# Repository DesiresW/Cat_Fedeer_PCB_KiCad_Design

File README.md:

# Comedero inteligente para gatos — PCB custom ESP32

## Descripción general

Este repositorio contiene el diseño de una **PCB custom basada en ESP32-S3** para un prototipo de comedero inteligente para gatos. El objetivo del proyecto no es construir una tarjeta de desarrollo genérica, sino una placa funcional orientada a controlar actuadores, leer sensores y permitir el monitoreo del comportamiento de alimentación de una mascota.

La PCB integra alimentación, programación, conexiones para sensores y actuadores, y módulos externos necesarios para el sistema. El diseño está pensado como una base de prototipado: permite validar el hardware, probar la lógica de control, registrar eventos y preparar una arquitectura donde el firmware pueda incorporar alertas o modelos simples de interpretación de comportamiento.

## Objetivo del proyecto

Diseñar y fabricar una PCB compacta, funcional y soldable que sirva como núcleo electrónico de un comedero para gatos con:

- Control de suministro sólido mediante servomotores.
- Control de motobomba para suministro líquido o sistema auxiliar.
- Medición de distancia mediante sensores ultrasónicos.
- Medición de peso mediante celda de carga y módulo HX711.
- Identificación mediante NFC.
- Alimentación regulada para el ESP32 y periféricos.
- Conexión de desarrollo separada de la conexión pensada para uso final.
- Posibilidad de integrar lógica de alertas e IA embebida en el firmware.

## Esquematico

## Estado actual

El proyecto se encuentra en fase de **prototipado físico**. La PCB ya fue diseñada, fabricada, soldada y puesta en pruebas iniciales. Aún se deben validar ajustes eléctricos, mecánicos y de distribución de pines, especialmente en los elementos que dependen de integración con sensores, actuadores y carcasa.

Este repositorio documenta el diseño actual, pero no debe asumirse como una versión final de producto.

## Arquitectura general del sistema

El sistema se organiza alrededor de un microcontrolador ESP32-S3, que actúa como núcleo de control y procesamiento. La placa conecta módulos externos y componentes SMD para manejar lectura sensórica, accionamiento y alimentación.

```text
                 ┌────────────────────────┐
                 │        ESP32-S3         │
                 │  Control + firmware     │
                 └───────────┬────────────┘
                             │
        ┌────────────────────┼────────────────────┐
        │                    │                    │
 ┌──────▼──────┐      ┌──────▼──────┐      ┌──────▼──────┐
 │ Ultrasonido │      │ HX711 +     │      │ PN532 NFC   │
 │ HC-SR04 x2  │      │ celda 1 kg  │      │ + tags NFC  │
 └─────────────┘      └─────────────┘      └─────────────┘
        │                    │                    │
        └────────────────────┼────────────────────┘
                             │
                 ┌───────────▼───────────┐
                 │ Actuadores             │
                 │ Servos + motobomba     │
                 └───────────────────────┘
```

## Funcionalidades previstas

### 1. Control de actuadores

La PCB contempla conexiones para servomotores y para una motobomba controlada mediante MOSFET NMOS. La intención es separar claramente las cargas de potencia del núcleo lógico del ESP32, evitando exigir corriente desde pines o líneas que no están diseñadas para eso.

Los servomotores se plantean para mecanismos de apertura, cierre o dosificación. La motobomba se contempla como actuador auxiliar para suministro líquido o pruebas de dispensación controlada.

### 2. Medición de distancia

Se decidió usar **dos sensores ultrasónicos HC-SR04** en lugar de sensores infrarrojos de bajo costo. La decisión se tomó porque los ultrasónicos entregan una lectura continua de distancia, mientras que varios sensores infrarrojos comerciales económicos solo entregan una señal binaria ajustada por umbral.

En este prototipo, una lectura continua resulta más útil para interpretar niveles, presencia o variaciones en superficies irregulares. Además, el costo de los ultrasónicos era considerablemente menor frente a algunos sensores infrarrojos disponibles comercialmente.

### 3. Medición de peso

El sistema contempla una celda de carga de 1 kg conectada a un módulo HX711. Esta etapa permite medir cambios de peso asociados al alimento o al recipiente.

En este diseño, las conexiones entre la celda de carga y la tarjeta HX711 se consideran externas al esquemático principal de la PCB, por lo que deben revisarse directamente según el módulo y la celda utilizados.

### 4. Identificación NFC

El módulo PN532 y los tags NFC se contemplan para identificación. En el contexto del comedero, esto puede utilizarse para asociar una mascota, un recipiente, una tarjeta de configuración o un evento específico del sistema.

La implementación final depende del firmware y del flujo de uso definido para el prototipo.

### 5. Firmware e IA embebida

El hardware está pensado para recopilar datos de sensores y habilitar una capa de interpretación en firmware. La IA no toma decisiones críticas de control por sí sola; su función prevista es apoyar la clasificación de eventos y generar alertas.

Una posible clasificación de comportamiento puede incluir:

- Estado normal o sin alerta.
- Posible hambre posterior al suministro.
- Rechazo de comida.
- Consumo menor al esperado.
- Consumo mayor al esperado.
- Comportamiento atípico.

Las decisiones de seguridad, apertura, suministro adicional o activación de actuadores deben permanecer en lógica convencional validada.

## Diseño de PCB

### Enfoque

El diseño no busca replicar una DevKit comercial. La PCB fue concebida como una tarjeta específica para el comedero, con las conexiones necesarias para el proyecto y con separación entre uso final y desarrollo.

El diseño prioriza:

- Integración del ESP32-S3 como microcontrolador principal.
- Conexiones para módulos externos.
- Alimentación regulada a 3.3 V.
- Línea de 5 V para periféricos que lo requieran.
- Protección básica en líneas de alimentación y actuadores.
- Componentes SMD para reducir volumen y mejorar integración.
- Conexión de programación separada para facilitar pruebas.

### Conexión de programación

La placa incluye una conexión pensada para desarrollo/programación mediante módulo externo tipo Pololu USB-C. A diferencia de los headers de sensores y actuadores, este conector se mantiene como **macho**, porque es una conexión móvil de desarrollo.

Esta decisión permite conservar una separación entre la interfaz técnica de programación y las conexiones que usaría un usuario final.

### Headers y conectores

Para las footprints de headers se recomienda mantener la lógica definida en el prototipo:

- Headers de sensores y actuadores: **SMD y hembra**.
- Header de programación Pololu: **macho**, con footprint modificada y funcional.
- Verificar siempre el orden de pines de la huella contra el pinout real del módulo, sensor o actuador.

Este punto es crítico porque algunos módulos comerciales no respetan el mismo orden de pines entre fabricantes o versiones.

### Etiquetado de señales

Los labels del diseño se dejaron referenciando al **componente** y no necesariamente al GPIO final. Esta decisión facilita el ruteo y permite cambiar GPIOs durante la organización de pistas sin perder claridad funcional.

Por eso, antes de cerrar una nueva versión, debe revisarse la correspondencia final entre:

- Label del esquemático.
- GPIO asignado.
- Pin físico del ESP32.
- Conector o módulo externo.
- Definición usada en firmware.

## Fabricación de la PCB

La PCB fue fabricada mediante un proceso de prototipado con máquina de fibra. El flujo usado fue:

1. Definición de pistas sobre cobre mediante máquina de fibra.
2. Aplicación de máscara de soldadura sobre la placa.
3. Segunda pasada con la máquina de fibra para retirar la máscara únicamente sobre los pads.
4. Soldadura de componentes SMD y módulos de conexión.
5. Pruebas iniciales de alimentación y funcionamiento.

Este proceso permitió obtener una placa física soldable sin depender de un servicio industrial tradicional de fabricación de PCBs, aunque requiere especial cuidado en pads, continuidad, máscara y tolerancias de soldadura.

## Componentes principales

| Bloque | Componente | Función |
|---|---|---|
| Control | ESP32-S3-WROOM-1-N8R8 | Microcontrolador principal del sistema |
| Alimentación | AMS1117-3.3 | Regulación de 5 V a 3.3 V |
| Programación | Pololu USB-C | Conexión de alimentación/programación para desarrollo |
| Identificación | PN532 NFC | Lectura NFC/RFID |
| Identificación | Tags NTAG213 | Etiquetas NFC para identificación |
| Distancia | HC-SR04 x2 | Medición continua de distancia |
| Peso | HX711 | Conversión y amplificación para celda de carga |
| Peso | Celda de carga 1 kg | Medición de peso |
| Actuación | Servomotores | Apertura/cierre/dosificación |
| Actuación | Motobomba | Suministro líquido o función auxiliar |
| Potencia | AO3400 | Conmutación de motobomba |
| Protección | SS34 | Diodo Schottky para protección |
| Filtrado | Capacitores 100 nF, 10 uF, 470 uF | Estabilidad y desacople |
| Señalización | LEDs SMD | Indicadores de 5 V y 3.3 V |
| Control manual | Pulsadores SMD | Reset y modo programación |

## Lista de referencias de compra

Estos enlaces son referencias de los componentes utilizados o considerados durante el prototipo. Antes de comprar o fabricar una nueva versión, se debe verificar disponibilidad, encapsulado, dimensiones y compatibilidad con la footprint usada en KiCad.

| Componente | Referencia / enlace |
|---|---|
| PN532 NFC | https://www.mercadolibre.com.co/kit-modulo-leitor-rfid-nfc-pn532-com-tag-e-carto/p/MCO2039743778 |
| Tags NFC NTAG213 | https://www.sigmaelectronica.net/producto/ntag213-nfc/ |
| Condensador 470 uF 6.3 V SMD | https://www.sigmaelectronica.net/producto/ct2917-470uf6-3v/ |
| Sensor ultrasónico HC-SR04 | https://www.sigmaelectronica.net/producto/hc-sr04/ |
| Tarjeta HX711 | https://www.sigmaelectronica.net/producto/tarjeta-hx711/ |
| Celda de carga 1 kg | https://www.sigmaelectronica.net/producto/celda-1k/ |
| Diodo SS34 | https://www.sigmaelectronica.net/producto/ss34/ |
| MOSFET AO3400 | https://www.mercadolibre.com.co/mosfet-ao3400-a09t-sot23-smd-x-5-unidades/up/MCOU3179338761 |
| Resistencia SMD 220 Ω | https://www.sigmaelectronica.net/producto/r1206-220-ohm/ |
| Resistencia SMD 1 kΩ | https://www.sigmaelectronica.net/producto/r0805-1k/ |
| Resistencia SMD 1.96 kΩ | https://www.sigmaelectronica.net/producto/p1-96kect/ |

## Inventario resumido de soldables

La siguiente lista resume los elementos principales identificados para fabricación de varias unidades del prototipo. Las cantidades exactas deben revisarse contra el Excel de inventario y la versión actual del esquemático.

| Elemento | Valor / referencia | Encapsulado o formato | Cantidad por PCB |
|---|---:|---|---:|
| Capacitor | 0.1 uF | 0603 | 6 |
| Capacitor | 10 uF | 1206 | 3 |
| Capacitor | 470 uF | SMD | 3 |
| LED | Rojo | 0805 | 1 |
| LED | Verde | 0805 | 1 |
| Diodo | SS34 | SMC / DO-214AB | 1 |
| Header macho | Programación | SMD, mínimo 8 pines | 1 |
| Header hembra | 3 pines | SMD | 2 |
| Header hembra | 4 pines | SMD | 4 |
| Header hembra | 2 pines | SMD | 1 |
| Conector/fuente | JRC-B008 | SMD | 1 |
| MOSFET | AO3400A | SOT-23 | 1 |
| Resistencia | 10 kΩ | 0603 | 5 |
| Resistencia | 120 Ω | 1206 | 1 |
| Resistencia | 68 Ω | 1206 | 1 |
| Resistencia | 330 Ω | 0805 | 2 |
| Resistencia | 220 Ω | 1206 | 1 |
| Resistencia | 1.96 kΩ | 1206 | 2 |
| Resistencia | 1 kΩ | 0805 | 2 |
| Pulsador | Switch SMD | SMD | 2 |
| Regulador | AMS1117-3.3 | SOT-223-3 | 1 |
| MCU | ESP32-S3-WROOM-1-N8R8 | Módulo SMD | 1 |

## Módulos externos considerados

| Módulo | Cantidad por PCB | Observación |
|---|---:|---|
| PN532 NFC | 1 | Módulo externo para lectura NFC |
| Motobomba | 1 | Controlada mediante MOSFET |
| HC-SR04 | 2 | Lecturas continuas de distancia |
| Celda de carga | 1 | Conectada al HX711 |
| HX711 | 1 | Módulo de lectura para celda de carga |
| Pololu programador | 1 | Uso de desarrollo/programación |
| Header hembra Pololu | 1 | Revisar orientación y pinout |
| Servomotores | 2 | Conectores dedicados |

## Recomendaciones de diseño y revisión

### Footprints

Antes de fabricar una nueva revisión de la PCB, revisar cuidadosamente:

- Que el encapsulado del componente comprado coincida con la footprint usada.
- Que las resistencias y capacitores SMD coincidan en tamaño real con el diseño.
- Que los headers SMD tengan la orientación correcta.
- Que el orden de pines de cada módulo coincida con la huella.
- Que los pads expuestos después de la máscara de soldadura sean suficientes para soldar cómodamente.
- Que el módulo ESP32 tenga área libre adecuada para antena.

### Inventario y Excel

Para actualizar el Excel del proyecto, conviene agrupar los componentes por valor y encapsulado. No es necesario repetir cada resistencia o capacitor en filas separadas si tienen el mismo valor y la misma footprint.

Una estructura útil sería:

| Componente | Valor | Encapsulado | Cantidad por PCB | Cantidad a fabricar | Total requerido | Disponible | Faltante | Tienda | Link |
|---|---|---|---:|---:|---:|---:|---:|---|---|

También es recomendable separar la lista por tienda:

- Sigma Electrónica: mayoría de resistencias, capacitores, sensores y módulos.
- Mercado Libre: PN532 y MOSFET AO3400, si no se consigue localmente en otra tienda.
- Electronilab: ESP32-S3-WROOM-1-N8R8, según disponibilidad.
- Otro proveedor: headers SMD hembra/macho si no están disponibles en Sigma.

### Alimentación

El diseño incluye regulación para 3.3 V y líneas de alimentación para periféricos. Como recomendación general:

- No alimentar servomotores ni motobomba desde el pin de 3.3 V del ESP32.
- Separar cargas de potencia y lógica siempre que sea posible.
- Usar capacitores de desacople cerca de alimentación del microcontrolador y módulos sensibles.
- Revisar caída de tensión cuando se activen actuadores.
- Validar temperatura del regulador durante pruebas.
- Confirmar continuidad y ausencia de cortos antes de montar el ESP32.

### Sensores ultrasónicos

Los sensores HC-SR04 operan típicamente a 5 V. Antes de conectar la señal `Echo` al ESP32, se debe revisar si se requiere adaptación de nivel hacia 3.3 V para proteger el pin del microcontrolador.

### Motobomba y MOSFET

Para la motobomba se contempla un MOSFET NMOS AO3400. La etapa debe revisarse con especial atención en:

- Corriente real de la motobomba.
- Diodo de protección.
- Tierra común entre lógica y potencia.
- Ancho de pista para corriente.
- Temperatura del MOSFET en funcionamiento.
- Separación entre señal de control y carga inductiva.

### Celda de carga y HX711

La celda de carga se conecta a la tarjeta HX711. En este repositorio, las conexiones entre celda y HX711 se consideran parte del cableado externo del módulo, no del esquemático principal de la PCB.

Antes de calibrar el sistema se debe:

- Verificar cableado de la celda.
- Confirmar orientación de alimentación.
- Probar lectura cruda del HX711.
- Calibrar con pesos conocidos.
- Registrar factor de calibración en firmware.

## Estructura sugerida del repositorio

```text
.
├── README.md
├── hardware/
│   ├── kicad/
│   │   ├── esquematico/
│   │   ├── pcb/
│   │   └── gerbers/
│   ├── renders/
│   └── fabricacion/
├── firmware/
│   ├── src/
│   ├── include/
│   └── README.md
├── docs/
│   ├── img/
│   │   └── pcb-soldada.jpg
│   ├── inventario/
│   └── pruebas/
└── tools/
    └── scripts/
```

Esta estructura es solo una recomendación para mantener separados el diseño electrónico, el firmware, las imágenes, la documentación y los archivos auxiliares.

## Pruebas recomendadas

Antes de conectar todos los módulos al mismo tiempo, se recomienda validar por etapas:

### 1. Prueba de continuidad

- Verificar continuidad de GND.
- Verificar ausencia de corto entre 5 V y GND.
- Verificar ausencia de corto entre 3.3 V y GND.
- Revisar continuidad de EN, IO0 y líneas de programación.
- Revisar pads expuestos y soldaduras frías.

### 2. Prueba de alimentación

- Energizar sin ESP32 si el diseño lo permite.
- Medir 5 V.
- Medir 3.3 V.
- Revisar temperatura del regulador.
- Confirmar comportamiento de LEDs de alimentación.
- Medir consumo en reposo.

### 3. Prueba de programación

- Conectar programador.
- Verificar enumeración USB/serial.
- Probar modo boot.
- Cargar firmware mínimo.
- Confirmar salida serial.

### 4. Prueba de sensores

- Leer HC-SR04 individualmente.
- Leer HX711 sin carga.
- Calibrar celda de carga.
- Probar PN532 con tag NFC.
- Registrar estabilidad de lecturas.

### 5. Prueba de actuadores

- Probar servos por separado.
- Probar motobomba con fuente adecuada.
- Confirmar que la activación de actuadores no reinicie el ESP32.
- Medir caída de tensión durante activación.
- Revisar ruido eléctrico o reinicios.

### 6. Prueba integrada

- Ejecutar un ciclo de alimentación simulado.
- Registrar distancia, peso y eventos.
- Probar identificación NFC.
- Validar que las alertas del firmware no activen cargas sin pasar por lógica convencional.
- Documentar errores encontrados para la siguiente revisión.

## Pendientes

- Validar pinout final de todos los headers.
- Confirmar si se requiere adaptación de nivel para señales de sensores a 5 V.
- Ajustar GPIOs según facilidad de ruteo y estabilidad del firmware.
- Documentar esquema final de alimentación.
- Subir fotografías del PCB soldado.
- Agregar capturas del esquemático y layout.
- Publicar archivos KiCad organizados.
- Documentar pruebas eléctricas realizadas.
- Documentar calibración de celda de carga.
- Definir estructura final del firmware.
- Separar con claridad la lógica convencional de la capa de IA.

## Advertencia

Este proyecto está en fase de prototipado. No debe usarse como circuito final sin validar alimentación, consumo, temperatura, aislamiento, protección, corriente de actuadores y seguridad mecánica. Cualquier modificación debe revisarse en esquemático, PCB y firmware antes de energizar la placa.

## Créditos

Proyecto desarrollado como ejercicio de diseño de PCB custom, sistemas embebidos e integración sensórica aplicada a un comedero inteligente para gatos.

El diseño toma como punto de partida la idea de construir una placa propia con ESP32, pero adapta el hardware a una aplicación específica: monitoreo y control de alimentación animal mediante sensores, actuadores y procesamiento embebido.

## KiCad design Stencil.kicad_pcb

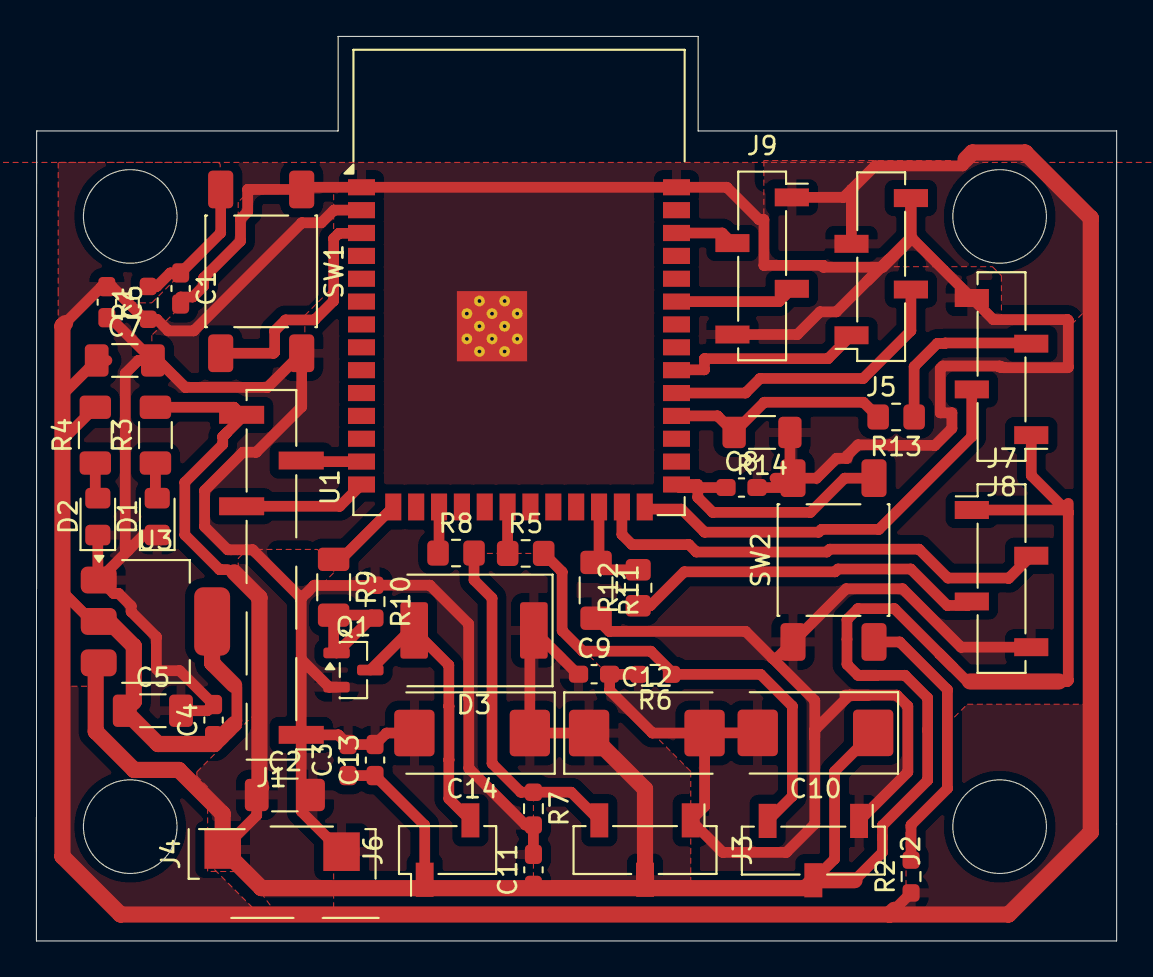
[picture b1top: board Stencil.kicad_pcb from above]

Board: 2 copper layers, 60.0 x 50.2 mm, 45 parts (0 on the bottom side), 26 nets.

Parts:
C1, C6, C8, C9, C11, C13: 0.1uF; C_0603_1608Metric_Pad1.08x0.95mm_HandSolder
C2, C5: 10u; C_1206_3216Metric_Pad1.33x1.80mm_HandSolder
C3, C4: 0.1u; C_0603_1608Metric_Pad1.08x0.95mm_HandSolder
C7: 10uF; C_1206_3216Metric_Pad1.33x1.80mm_HandSolder
C10, C12, C14: 470uF; CP_EIA-7343-31_Kemet-D_HandSolder
D1: RED; LED_0805_2012Metric_Pad1.15x1.40mm_HandSolder
D2: GREEN; LED_0805_2012Metric_Pad1.15x1.40mm_HandSolder
D3: SS34; ST_D_SMC
J1: Conn_01x04_Pin; pololu
J2: Servo 2; PinSocket_1x03_P2.54mm_Vertical_SMD_Pin1Left
J3: Servo 1; PinSocket_1x03_P2.54mm_Vertical_SMD_Pin1Left
J4: Conn_01x02_Pin; JRC-B008
J5: Sensor NFC ↓; PinSocket_1x04_P2.54mm_Vertical_SMD_Pin1Right
J6: Motobomba; PinSocket_1x02_P2.54mm_Vertical_SMD_Pin1Left
J7: Ultrasónico 1; PinSocket_1x04_P2.54mm_Vertical_SMD_Pin1Left
J8: Ultrasónico 2; PinSocket_1x04_P2.54mm_Vertical_SMD_Pin1Left
J9: ↑Celda_Carga; PinSocket_1x04_P2.54mm_Vertical_SMD_Pin1Right
Q1: NMOS ↓; SOT-23
R1, R2, R6, R7, R10: 10k; R_0603_1608Metric_Pad0.98x0.95mm_HandSolder
R3: 120; R_1206_3216Metric_Pad1.30x1.75mm_HandSolder
R4: 68; R_1206_3216Metric_Pad1.30x1.75mm_HandSolder
R5, R8: 330; R_0805_2012Metric_Pad1.20x1.40mm_HandSolder
R9: 220; R_1206_3216Metric_Pad1.30x1.75mm_HandSolder
R11, R14: 1.96k; R_1206_3216Metric_Pad1.30x1.75mm_HandSolder
R12, R13: 1k; R_0805_2012Metric_Pad1.20x1.40mm_HandSolder
SW1: Reinicio; SW_Push_1P1T_NO_E-Switch_TL3301NxxxxxG
SW2: Programar; SW_Push_1P1T_NO_E-Switch_TL3301NxxxxxG
U1: ESP32-S3-WROOM-1
U3: AMS1117-3.3; SOT-223-3_TabPin2

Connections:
3V3: C4.1, C5.1, C6.1, C7.1, J5.3, J9.1, R1.1, R2.1, R4.2, U1.2 (3V3), U3.2 (VO)
D+: J1.3, U1.14 (USB_D+)
D-: J1.2, U1.13 (USB_D-)
DT1: J9.3, U1.35 (IO42)
EC1: R11.1, R12.2, U1.24 (IO47)
EC2: R13.2, R14.2, U1.30 (IO37)
EN: C1.1, R1.2, SW1.2, U1.3 (EN)
GND: C1.2, C2.2, C3.2, C4.2, C5.2, C6.2, C7.2, C8.2, C9.2, C10.2, C11.2, C12.2, C13.2, C14.2, D1.1 (K), D2.1 (K), J1.4, J2.1, J3.1, J4.2, J5.4, J7.4, J8.4, J9.4, Q1.2 (S), R6.2, R7.2, R10.1, R11.2, R14.1, SW1.1, SW2.1, U1.1 (GND), U1.40 (GND), U1.41 (GND), U3.1 (GND)
IO0: C8.1, R2.2, SW2.2, U1.27 (IO0)
MB1: R9.1, U1.15 (IO3)
unnamed: D1.2 (A), R3.1
unnamed: D2.2 (A), R4.1
unnamed: D3.2 (A), J6.2, Q1.3 (D)
unnamed: J2.3, R5.2, R6.1
unnamed: J3.3, R7.1, R8.2
unnamed: J7.3, R12.1
unnamed: J8.3, R13.1
unnamed: Q1.1 (G), R9.2, R10.2
SCK1: J9.2, U1.38 (IO2)
SCL-NFC: J5.1, U1.32 (IO39)
SDA-NFC: J5.2, U1.31 (IO38)
SM1: R5.1, U1.20 (IO12)
SM2: R8.1, U1.17 (IO9)
TR1: J7.2, U1.25 (IO48)
TR2: J8.2, U1.26 (IO45)
VCC_5V: C2.1, C3.1, C9.1, C10.1, C11.1, C12.1, C13.1, C14.1, D3.1 (K), J1.1, J2.2, J3.2, J4.1, J6.1, J7.1, J8.1, R3.2, U3.3 (VI)

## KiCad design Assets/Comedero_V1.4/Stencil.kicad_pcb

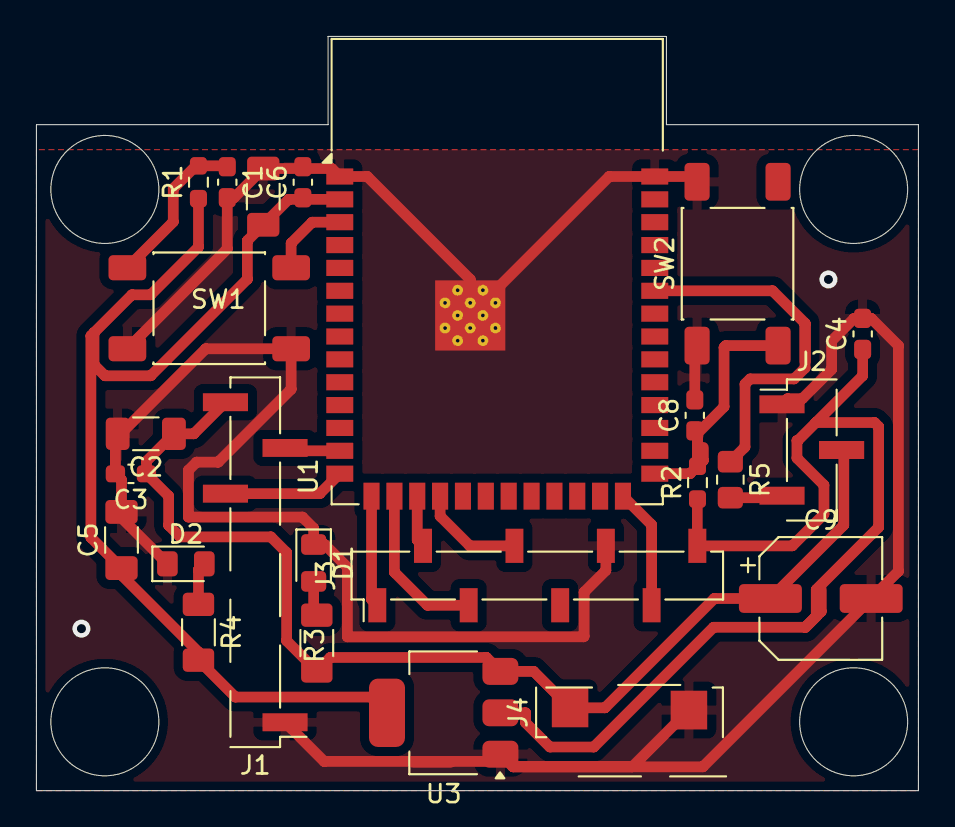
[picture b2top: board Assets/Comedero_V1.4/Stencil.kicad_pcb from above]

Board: 2 copper layers, 49.0 x 41.9 mm, 24 parts (0 on the bottom side), 15 nets.

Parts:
C1, C6, C8: 0.1uF; C_0603_1608Metric_Pad1.08x0.95mm_HandSolder
C2, C5: 10u; C_1206_3216Metric_Pad1.33x1.80mm_HandSolder
C3, C4: 0.1u; C_0603_1608Metric_Pad1.08x0.95mm_HandSolder
C7: 10uF; C_1206_3216Metric_Pad1.33x1.80mm_HandSolder
C9: 100uF; CP_Elec_6.3x5.4
D1: RED; LED_0805_2012Metric_Pad1.15x1.40mm_HandSolder
D2: GREEN; LED_0805_2012Metric_Pad1.15x1.40mm_HandSolder
J1: Conn_01x04_Pin; PinHeader_1x08_P2.54mm_Vertical_SMD_Pin1Left
J2: Conn_01x03_Pin; PinHeader_1x03_P2.54mm_Vertical_SMD_Pin1Left
J3: Conn_01x08_Socket; PinSocket_1x08_P2.54mm_Vertical_SMD_Pin1Left
J4: Conn_01x02_Pin; PinHeader_1x04_P2.54mm_Vertical_SMD_Pin1Left
R1, R2: 10k; R_0603_1608Metric_Pad0.98x0.95mm_HandSolder
R3: 120; R_1206_3216Metric_Pad1.30x1.75mm_HandSolder
R4: 68; R_1206_3216Metric_Pad1.30x1.75mm_HandSolder
R5: 330; R_0805_2012Metric_Pad1.20x1.40mm_HandSolder
SW1, SW2: SW_Push; SW_Push_1P1T_NO_E-Switch_TL3301NxxxxxG
U1: ESP32-S3-WROOM-1
U3: AMS1117-3.3; SOT-223-3_TabPin2

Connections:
3V3: C4.1, C5.1, C6.1, C7.1, J3.8, R1.1, R2.1, R4.2, U1.2 (3V3), U3.2 (VO)
D+: J1.3, U1.14 (USB_D+)
D-: J1.2, U1.13 (USB_D-)
EN: C1.1, R1.2, SW1.2, U1.3 (EN)
GND: C1.2, C2.2, C3.2, C4.2, C5.2, C6.2, C7.2, C8.2, C9.2, D1.1 (K), D2.1 (K), J1.4, J2.1, J3.6, J4.2, SW1.1, SW2.1, U1.1 (GND), U1.40 (GND), U1.41 (GND), U3.1 (GND)
GPIO_15: J3.1, U1.15 (IO3)
GPIO_16: J3.3, U1.16 (IO46)
GPIO_17: J3.2, U1.17 (IO9)
GPIO_18: J3.4, U1.18 (IO10)
GPIO_26: J3.7, U1.26 (IO45)
IO0: C8.1, R2.2, SW2.2, U1.27 (IO0)
unnamed: D1.2 (A), R3.1
unnamed: D2.2 (A), R4.1
unnamed: J2.3, R5.2
VCC_5V: C2.1, C3.1, C9.1, J1.1, J2.2, J4.1, R3.2, U3.3 (VI)

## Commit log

2026-05-15 Primer commit: diseño PCB comedero para gatos
2026-05-15 Change PCB image paths in README.md
    Updated image references in README for PCB prototype.
2026-05-15 Fix image path for PCB prototype
    Update image path for PCB prototype in README
2026-05-15 Replace PCB image and add schematic section
    Updated images in README and added schematic section.
